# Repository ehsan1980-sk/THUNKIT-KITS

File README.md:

# About #

Thunkit Electronics sells electronic kits for hobbyists and engineers alike. Available at [thunkitelectronics.com](https://thunkitelectronics.com) and [Tindie](https://www.tindie.com/stores/cmccaskey). All designs are open source with schematics, board layouts, code, and BOMs freely available.

## In This Repository ##
| POGO ICSP | BREADBOARD ICSP | LOGIC-KEYCHAIN | MAKIT-THT | T85DUINO |
| ------------------------------------------ | ----------------------------------------- | ----------------------------------------- | ----------------------------------------- | ----------------------------------------- |
|  |  |  |  |  |
| Spring loaded pogo pins for AVR ICSP programming | Breakout for AVR ICSP Cable | D flip-flop SMD soldering keychain kit | DIY 100% Through-hole Arduino kit | DIY 100% Through-hole Mini Arduino kit |

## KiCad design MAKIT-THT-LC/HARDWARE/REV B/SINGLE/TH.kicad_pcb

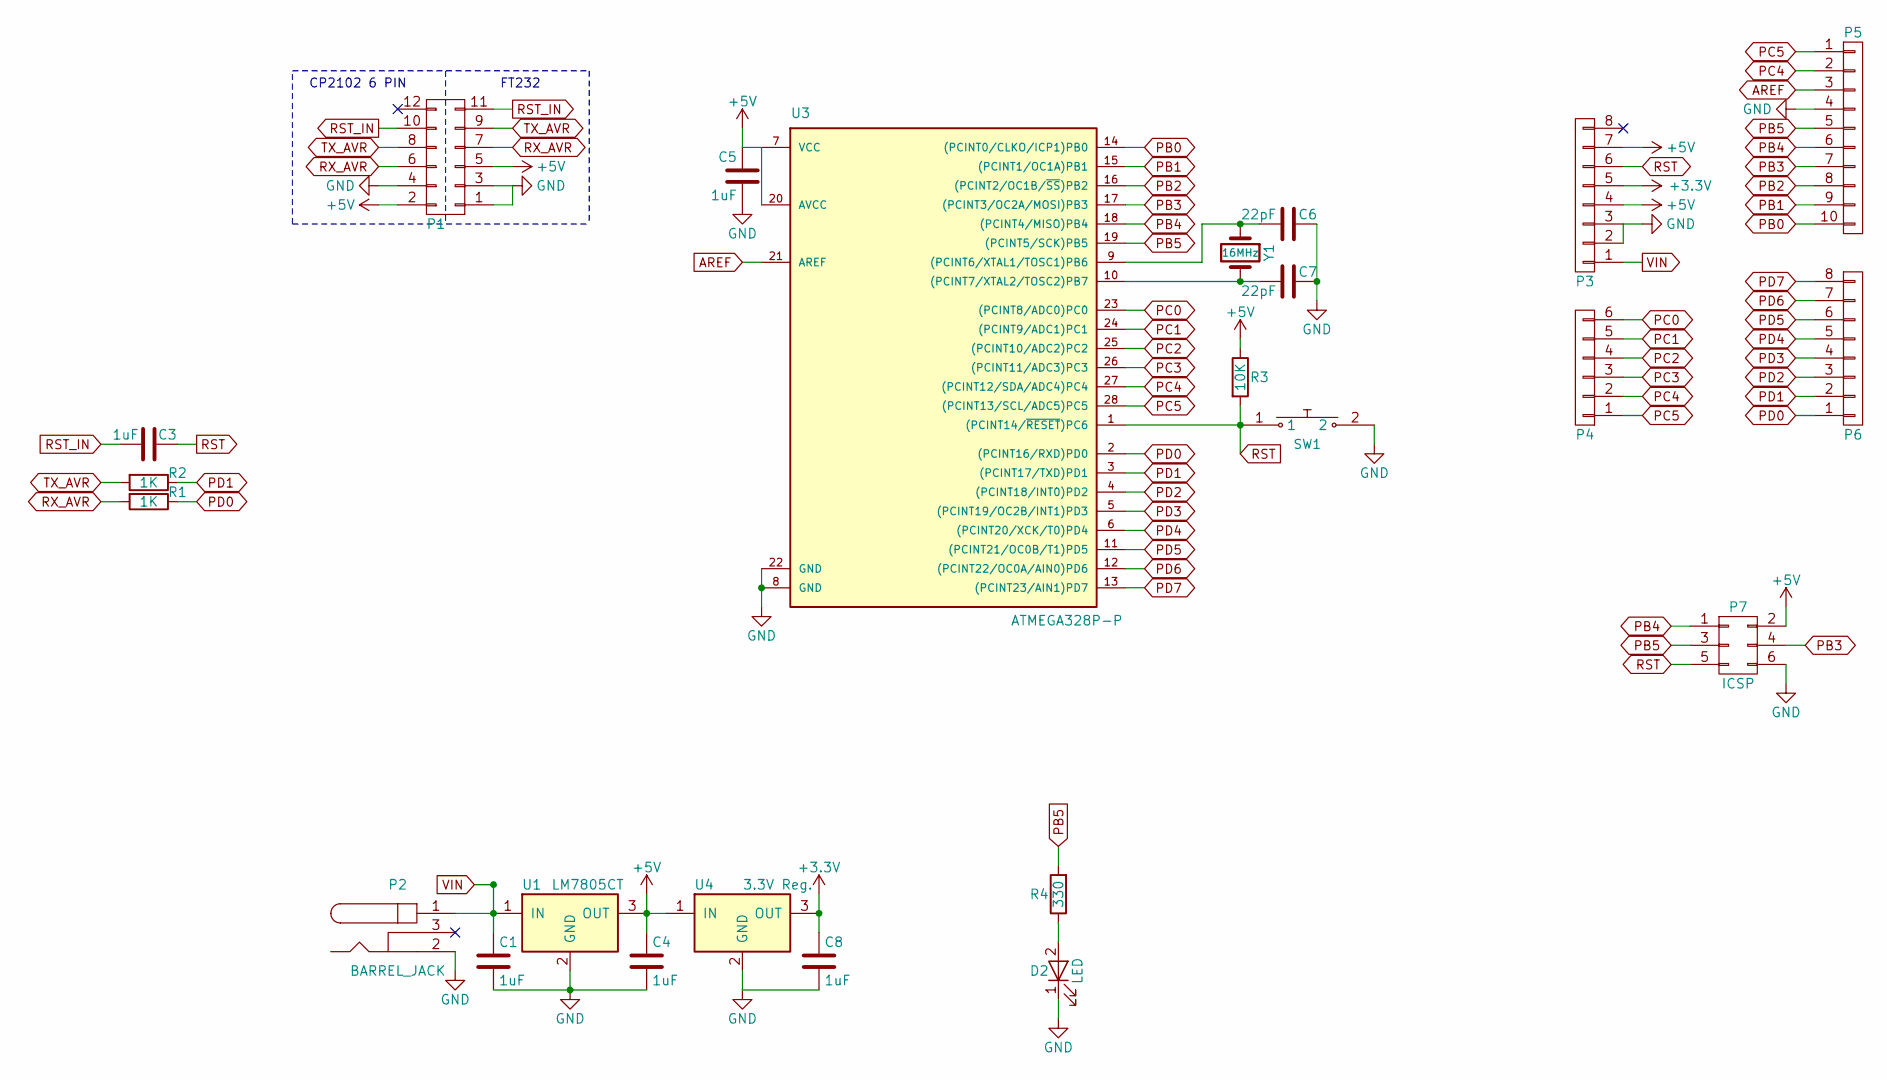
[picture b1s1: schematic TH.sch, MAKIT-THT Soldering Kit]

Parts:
C1, C3, C4, C5, C8: 1uF; C_Disc_D3.8mm_W2.6mm_P2.50mm
C6, C7: 22pF; C_Disc_D3.8mm_W2.6mm_P2.50mm
D2: LED; LED_D5.0mm
P1: CONN_02X06; Pin_Header_Angled_2x06
P2: BARREL_JACK
P3, P6: CONN_01X08; Pin_Header_Straight_1x08_Pitch2.54mm
P4: CONN_01X06; Pin_Header_Straight_1x06_Pitch2.54mm
P5: CONN_01X10; Pin_Header_Straight_1x10_Pitch2.54mm
P7: ICSP; Pin_Header_Straight_2x03_Pitch2.54mm
R1, R2: 1K; R_Axial_DIN0207_L6.3mm_D2.5mm_P7.62mm_Horizontal
R3: 10K; R_Axial_DIN0207_L6.3mm_D2.5mm_P7.62mm_Horizontal
R4: 330; R_Axial_DIN0207_L6.3mm_D2.5mm_P7.62mm_Horizontal
SW1: Push_SW; SW_PUSH_6mm
U1: LM7805CT; TO-220-3_Horizontal_NO_HOLE
U3: ATMEGA328P-P; DIP-28_W7.62mm_LongPads
U4: 3.3V Reg.; TO-92_Inline_Wide
Y1: 16MHz; Crystal_HC49-U_Vertical

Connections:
+3V3: C8.1, P3.5, U4.3 (OUT)
+5V: C4.1, C5.1, P1.2, P1.5, P3.4, P3.7, P7.2, R3.1, U1.3 (OUT), U3.7 (VCC), U3.20 (AVCC), U4.1 (IN)
AREF: P5.3, U3.21 (AREF)
GND: C1.2, C4.2, C5.2, C6.1, C7.1, C8.2, D2.1 (K), P1.1, P1.3, P1.4, P2.2, P3.2, P3.3, P5.4, P7.6, SW1.2, U1.2 (GND), U3.8 (GND), U3.22 (GND), U4.2 (GND)
unnamed: C6.2, U3.9 ((PCINT6/XTAL1/TOSC1)PB6), Y1.1
unnamed: C7.2, U3.10 ((PCINT7/XTAL2/TOSC2)PB7), Y1.2
unnamed: D2.2 (A), R4.1
PB0: P5.10, U3.14 ((PCINT0/CLKO/ICP1)PB0)
PB1: P5.9, U3.15 ((PCINT1/OC1A)PB1)
PB2: P5.8, U3.16 ((PCINT2/OC1B/~SS~)PB2)
PB3: P5.7, P7.4, U3.17 ((PCINT3/OC2A/MOSI)PB3)
PB4: P5.6, P7.1, U3.18 ((PCINT4/MISO)PB4)
PB5: P5.5, P7.3, R4.2, U3.19 ((PCINT5/SCK)PB5)
PC0: P4.6, U3.23 ((PCINT8/ADC0)PC0)
PC1: P4.5, U3.24 ((PCINT9/ADC1)PC1)
PC2: P4.4, U3.25 ((PCINT10/ADC2)PC2)
PC3: P4.3, U3.26 ((PCINT11/ADC3)PC3)
PC4: P4.2, P5.2, U3.27 ((PCINT12/SDA/ADC4)PC4)
PC5: P4.1, P5.1, U3.28 ((PCINT13/SCL/ADC5)PC5)
PD0: P6.1, R1.1, U3.2 ((PCINT16/RXD)PD0)
PD1: P6.2, R2.1, U3.3 ((PCINT17/TXD)PD1)
PD2: P6.3, U3.4 ((PCINT18/INT0)PD2)
PD3: P6.4, U3.5 ((PCINT19/OC2B/INT1)PD3)
PD4: P6.5, U3.6 ((PCINT20/XCK/T0)PD4)
PD5: P6.6, U3.11 ((PCINT21/OC0B/T1)PD5)
PD6: P6.7, U3.12 ((PCINT22/OC0A/AIN0)PD6)
PD7: P6.8, U3.13 ((PCINT23/AIN1)PD7)
RST: C3.2, P3.6, P7.5, R3.2, SW1.1, U3.1 ((PCINT14/~RESET~)PC6)
RST_IN: C3.1, P1.10, P1.11
RX_AVR: P1.6, P1.7, R1.2
TX_AVR: P1.8, P1.9, R2.2
VIN: C1.1, P2.1, P3.1, U1.1 (IN)

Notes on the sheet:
FT232
CP2102 6 PIN

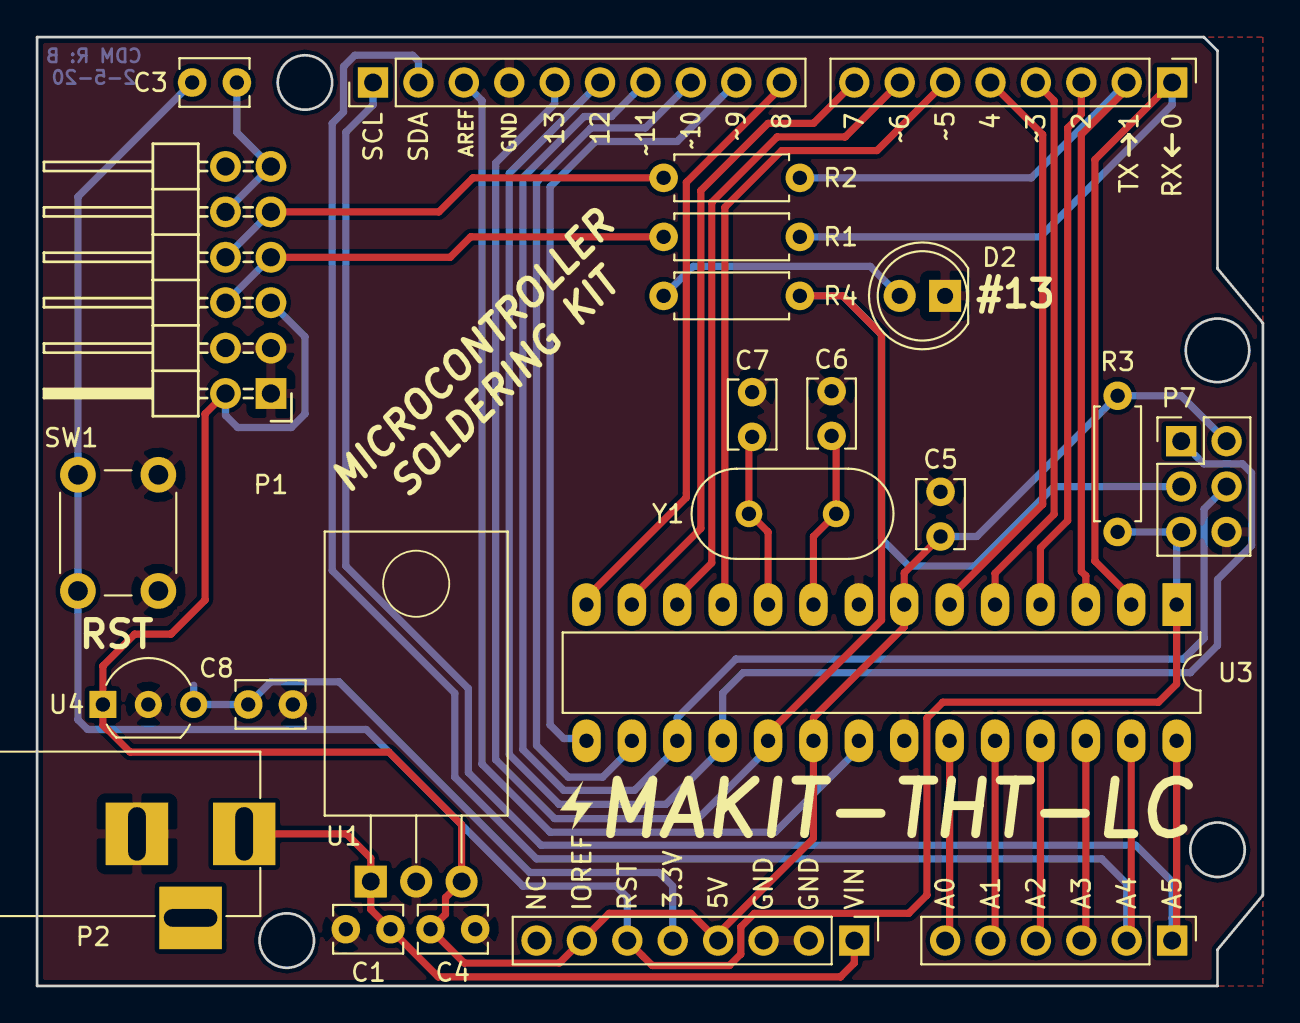
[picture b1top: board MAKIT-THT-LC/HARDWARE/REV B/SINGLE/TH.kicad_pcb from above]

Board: 2 copper layers, 68.6 x 53.1 mm, 24 parts (0 on the bottom side), 32 nets.

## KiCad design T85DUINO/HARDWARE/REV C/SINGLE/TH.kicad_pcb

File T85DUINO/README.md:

# About #

Thunkit Electronics sells electronic kits for hobbyists and engineers alike. Available at [thunkitelectronics.com](https://thunkitelectronics.com) and [Tindie](https://www.tindie.com/stores/cmccaskey). All designs are open source with schematics, board layouts, code, and BOMs freely available.

## Description ###
 <br />
The T85DUINO is a mini Arduino board featuring the ATTiny85. The T85DUINO is a 3V board powered by a CR1025 battery making this a great choice to show off your soldering and programming skills if you choose to wear it as a badge.

## Why T85DUINO? ##
The T85DUINO is a mini Arduino kit. This makes the T85DUINO a simple yet fun soldering kit that has the added value of being a development board for the ATtiny85 after assembly. The T85DUINO can be used as a development board, directly in your project, or even a badge to show off your soldering and programming skills.

## Technical Specifications ##

The T85DUINO uses the ATtiny85 as the main microconroller. The ATtiny85 is flashed with Gemma boot by Adafruit that allows the T85DUINO to be reprogrammed in the Arduino IDE. 

The T85DUINO runs directly off of 3V from a CR1025 battery. While this is enough to blink the on-board LED, it is posible to brown out the microcontroller if the external connections on the board are used without consideration to this fact.

Since the T85DUINO runs at 3V, the board only requires the 68 Ohm termination resistors for USB and doesn't require the zener diodes to limit the USB data line voltages.

The T85DUINO has an on-board LED that can be blinked to emulate the famous Blink Arduino Sketch.

## Schematic ##
PDF coming soon...Please check KiCad files

## Bill of Material ##
PDF coming soon...Please check KiCad files

## Soldering Instructions ##
Coming soon...

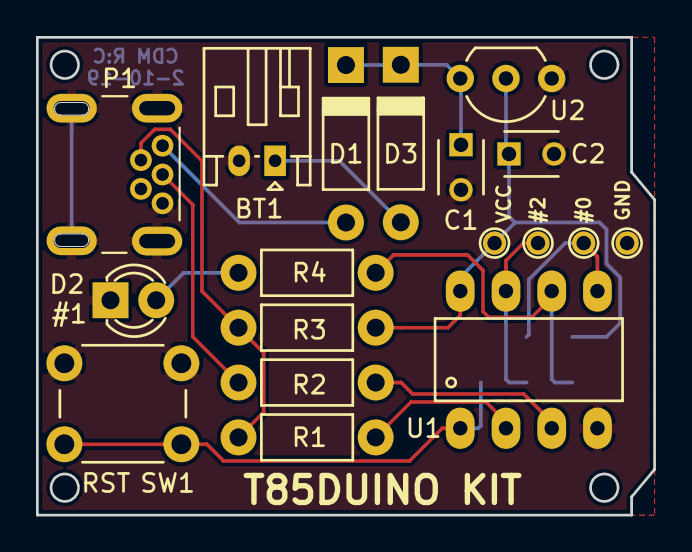
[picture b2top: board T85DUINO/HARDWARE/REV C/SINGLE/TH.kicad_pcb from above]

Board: 2 copper layers, 34.3 x 26.5 mm, 19 parts (1 on the bottom side), 14 nets.

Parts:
BT1: JST-PH; JST_PH_S2B-PH-K_02x2.00mm_Angled
C1, C2: 1uF; C_Disc_D3_P2.5
D1, D3: D_Schottky; DO-41_Short
D2: LED; LED-3MM
P1: USB_OTG; USB_MINI_B_TH
P2: ICSP; 2.54 ICSP
R1, R2: 68; Resistor_Horizontal_RM7mm
R3: 1.5K; Resistor_Horizontal_RM7mm
R4: 330; Resistor_Horizontal_RM7mm
SW1: Push_SW; SW_PUSH_6mm
TP1, TP2, TP3, TP4: TEST; PINTST
U1: ATTINY85-P; DIP-8
U2: AP1117; TO-92_Inline_Wide

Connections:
GND: BT1.2, C1.2, C2.2, D2.1, P1.5, P1.6, P2.6, SW1.2, TP3.1, U1.4, U2.1
MISO: P2.1, R4.2, U1.6
MOSI: P2.4, TP1.1, U1.5
unnamed: BT1.1, D3.2
unnamed: C1.1, D1.1, D3.1, U2.3
unnamed: D2.2, R4.1
unnamed: P1.2, R1.2, R3.2
unnamed: P1.3, R2.2
unnamed: R1.1, U1.2
unnamed: R2.1, U1.3
RST: P2.5, SW1.1, U1.1
SCK: P2.3, TP2.1, U1.7
VBUS: D1.2, P1.1
VCC: C2.1, P2.2, R3.1, TP4.1, U1.8, U2.2

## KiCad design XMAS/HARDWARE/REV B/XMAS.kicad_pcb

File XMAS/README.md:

# About #

Thunkit Electronics sells electronic kits for hobbyists and engineers alike. Available at [thunkitelectronics.com](https://thunkitelectronics.com) and [Tindie](https://www.tindie.com/stores/cmccaskey). All designs are open source with schematics, board layouts, code, and BOMs freely available.

## Description ###
 <br />
The Thunkit Electronics Christmas Ornament is a trendy PCB christmas ornament that lights up 18 cool while LEDs in a spiral pattern. This is light sensitive and only triggers in the dark in 30 second intervals. Powered by a CR2032 battery, battery life is approximately 4 months due to the heavy use of interrupts for timing.

Note: Board shown is REV A, REV B has small tweaks to the layout and the removal of the bodge wire near the microcontroller.

## Schematic ##

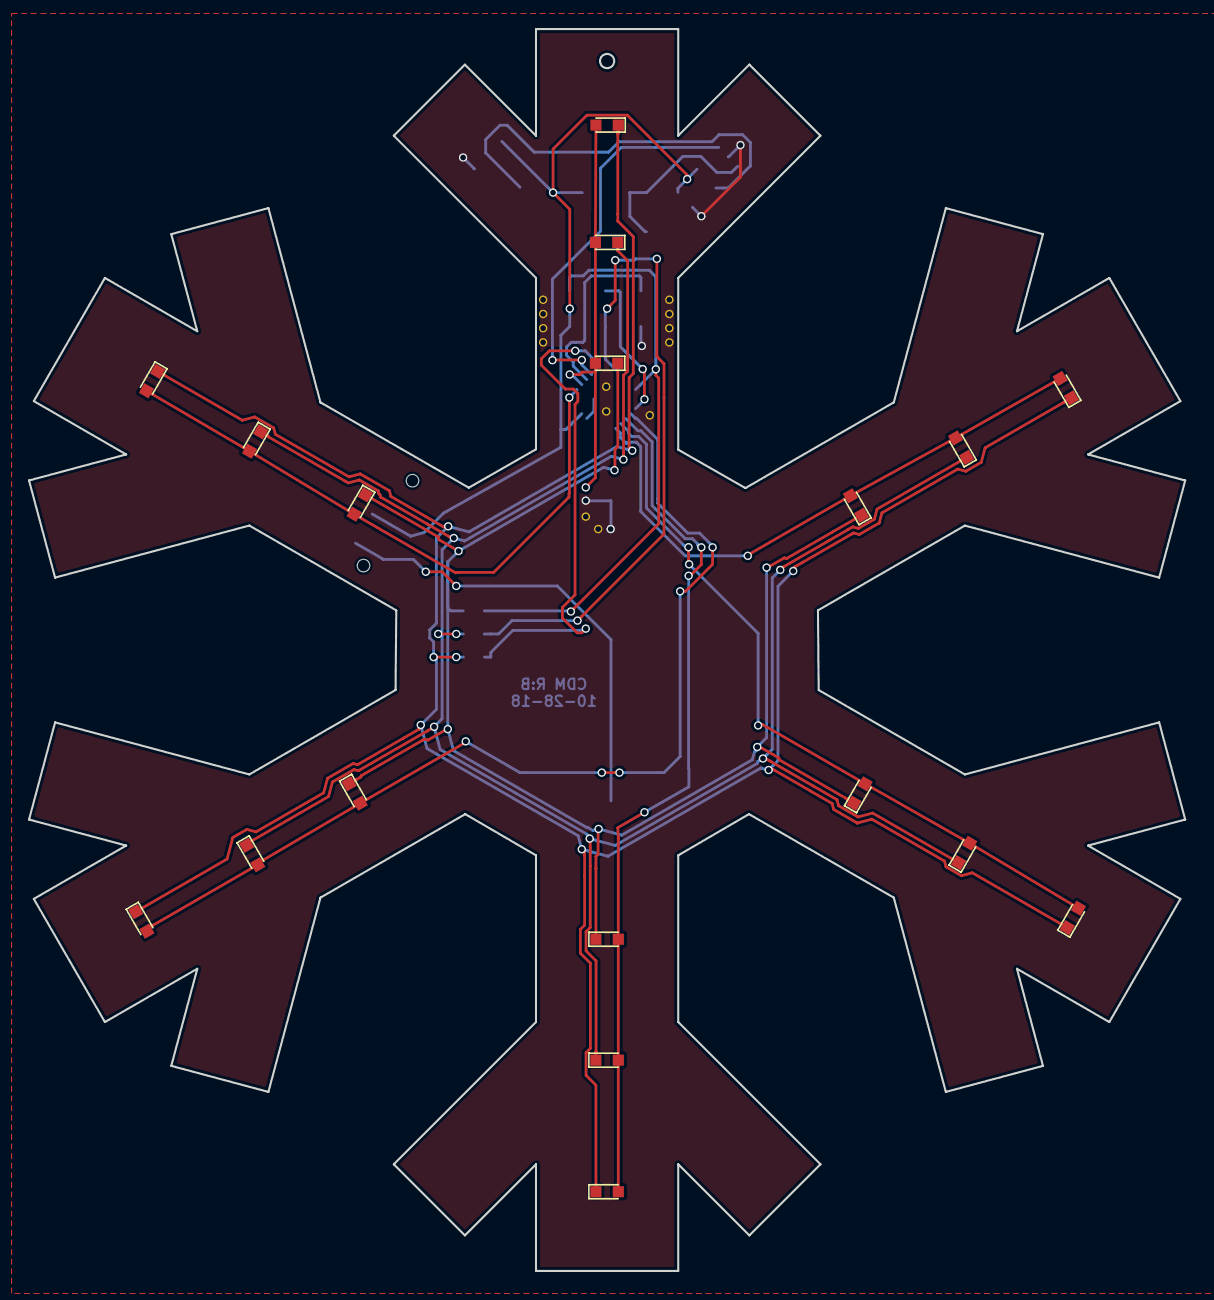
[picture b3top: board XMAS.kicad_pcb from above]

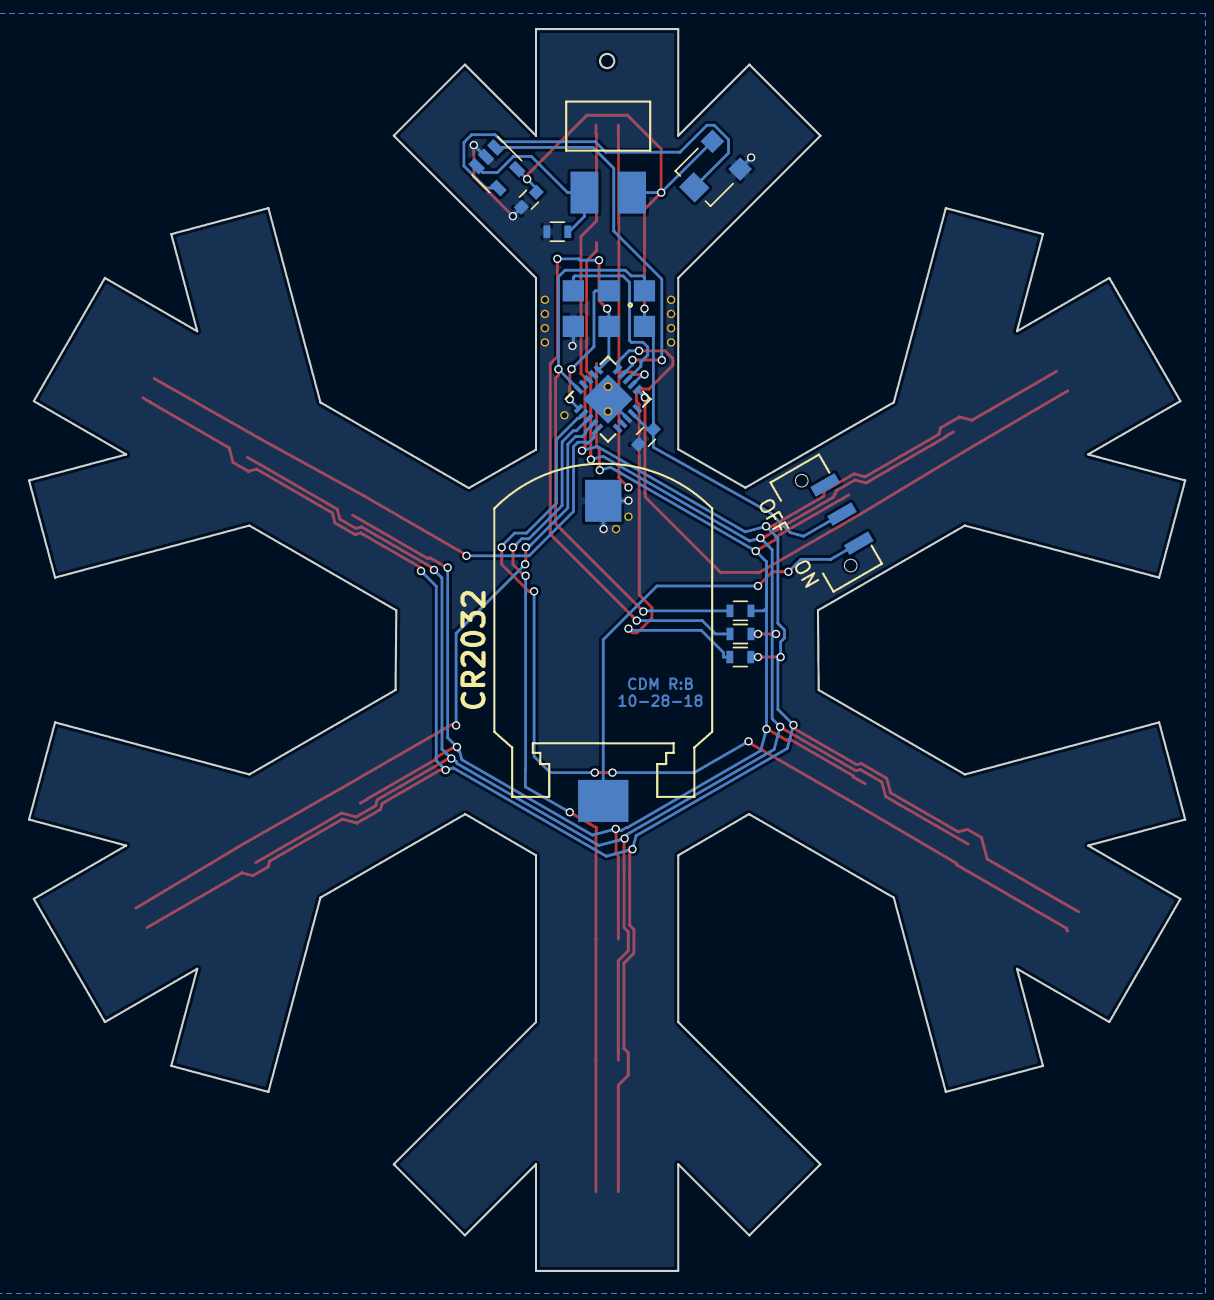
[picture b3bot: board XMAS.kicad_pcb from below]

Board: 2 copper layers, 82.6 x 88.7 mm, 31 parts (13 on the bottom side), 20 nets.

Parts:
BT1: CR2032; CR2032HARWIN
C1, C2: C; C_0603
D1, D2, D3, D4, D5, D6, D7, D8, D9, D10, D11, D12, D13, D14, D15, D16, D17, D18: LED; LED_0603
P1: ICSP; 2.54 ICSP
R1, R2, R3, R8: R; R_0603
R7: R_PHOTO; SMT_PHOTORESISTOR
RV1: POT; Potentiometer_Trimmer-EVM3E
SW1: Push_SW; JS102011JAQN_Handsoldering
U1: MCP6541T-I/LT; SOT-23-5
U2: ATTINY24A-M; QFN-20-1EP_4x4mm_Pitch0.5mm

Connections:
A1: D1.2, D7.2, D13.2, U2.5
A2: D2.2, D8.2, D14.2, U2.4
A3: D3.2, D9.2, D15.2, U2.3
A4: D4.2, D10.2, D16.2, U2.2
A5: D5.2, D11.2, D17.2, U2.11
A6: D6.2, D12.2, D18.2, U2.12
C1: P1.1, R1.1, U2.20
C2: P1.4, R2.1, U2.16
C3: R3.1, U2.15
GND: BT1.2, C1.2, C2.1, P1.6, R8.2, RV1.1, U1.2, U2.8
INT0_AVR: U1.1, U2.14
unnamed: BT1.1, SW1.1
unnamed: D1.1, D2.1, D3.1, D4.1, D5.1, D6.1, R1.2
unnamed: D7.1, D8.1, D9.1, D10.1, D11.1, D12.1, R2.2
unnamed: D13.1, D14.1, D15.1, D16.1, D17.1, D18.1, R3.2
unnamed: R7.2, R8.1, U1.3
unnamed: RV1.2, U1.4
RST: P1.5, U2.13
SCK: P1.3, U2.1
VCC: C1.1, C2.2, P1.2, R7.1, RV1.3, SW1.2, U1.5, U2.9

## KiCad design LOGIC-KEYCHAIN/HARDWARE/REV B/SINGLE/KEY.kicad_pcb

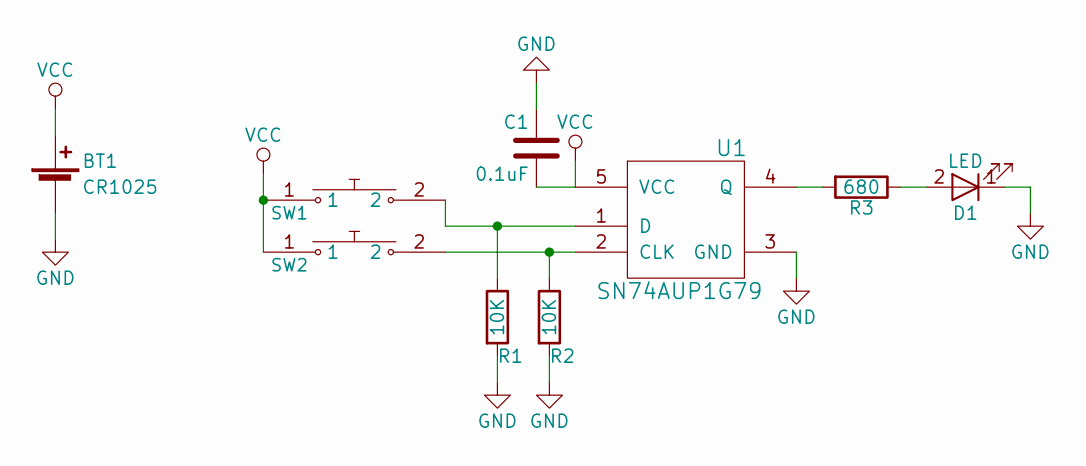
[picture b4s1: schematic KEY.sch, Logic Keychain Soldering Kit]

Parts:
BT1: CR1025; BK-870
C1: 0.1uF; C_0603
D1: LED; LED_0603
R1, R2: 10K; R_0603
R3: 680; R_0603
SW1, SW2: Push_SW; PTS810 SJK 250 SMTR LFS_Handsoldering
U1: SN74AUP1G79; SOT-23-5

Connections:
GND: BT1.2 (-), C1.1, D1.1 (K), R1.2, R2.2, U1.3 (GND)
unnamed: D1.2 (A), R3.1
unnamed: R1.1, SW1.2, U1.1 (D)
unnamed: R2.1, SW2.2, U1.2 (CLK)
unnamed: R3.2, U1.4 (Q)
VCC: BT1.1 (+), C1.2, SW1.1, SW2.1, U1.5 (VCC)

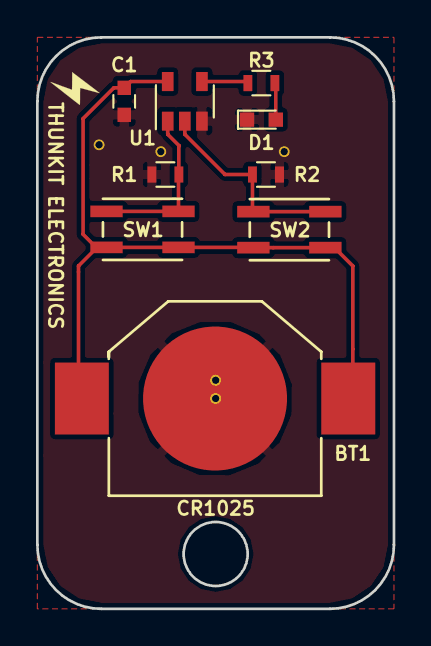
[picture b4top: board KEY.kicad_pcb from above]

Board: 2 copper layers, 19.8 x 31.8 mm, 9 parts (0 on the bottom side), 6 nets.

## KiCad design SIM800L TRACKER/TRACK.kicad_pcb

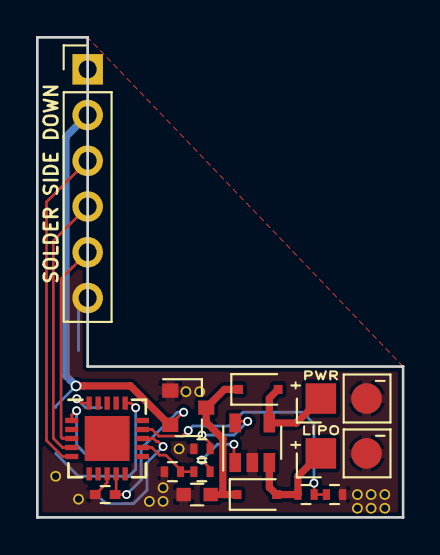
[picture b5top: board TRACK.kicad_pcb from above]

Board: 2 copper layers, 20.3 x 26.7 mm, 16 parts (1 on the bottom side), 16 nets.

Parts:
BT1: 1S; Pin_Header_Straight_1x02_Pitch2.54mm
C1: 4.7uF; C_0603
C2: 1uF; C_0402
D1, D2: S; D_SOD-323F
P1: PWR; Pin_Header_Straight_1x02_Pitch2.54mm
P2: ICSP; 2.54 ICSP
P3: SIM800L Coreboard; Pin_Header_Straight_1x06_Pitch2.54mm
R1, R2, R4, R5: 10K; R_0402
R3: 2K; R_0402
U1: MCP73831T; SOT-23-5
U2: AP1117; SOT-23
U3: ATTINY841-MU; QFN-20-1EP_4x4mm_Pitch0.5mm

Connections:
AVR_RST: P2.5, U3.13
BT_VCC: R4.1, R5.2, U3.14
CHRG_STAT: R1.2, R2.1, U3.12
GND: BT1.2, C1.2, C2.2, P1.2, P2.6, P3.6, R1.1, R3.2, R5.1, U1.2, U2.1, U3.8
MISO: P2.1, U3.20
MOSI: P2.4, U3.16
unnamed: BT1.1, D2.2, R4.2, U1.3
unnamed: D1.2, P1.1, U1.4
unnamed: R2.2, U1.1
unnamed: R3.1, U1.5
SCK: P2.3, U3.1
SIM_RST: P3.3, U3.5
SIM_RX: P3.4, U3.4
SIM_TX: P3.5, U3.3
VCC: C2.1, P2.2, P3.2, U2.2, U3.9
VIN: C1.1, D1.1, D2.1, U2.3

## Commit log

2018-07-04 test3
2018-07-04 fixed gitignore file
2018-07-04 test4
2018-07-16 replaced A7 for SIM 800L
2018-09-09 file recovery and updates
2018-09-22 fixed breadboard layer issues
2018-09-24 logic keychain D FF update
2018-10-09 MAKIT-THT REV C
2018-10-10 keychain FF BOM matches schematic
2018-10-15 readme and images
2018-10-15 readme updates
2018-10-15 MAKIT rev c
2018-10-24 readme update
2018-10-24 readme link fix
2018-10-24 link fix
2018-11-07 added some repos, changed names of others
2018-11-07 added christmas ornament
2018-11-08 removed makit soldering inst, updated readme
2018-11-08 fixed readme image links
2018-11-08 fixed T85DUINO readme
2018-11-08 readme
2018-11-11 updated title block
2018-11-11 rev b and license
2018-11-25 updated XMAS
2018-12-08 readme, code, makefile
2019-03-18 march update
2019-04-23 updated vreg
2019-04-23 3.3V Reg BOM update
2020-03-17 added MAKIT-THT-LC
2020-03-17 cleanup
2022-01-31 Create Think it-Arduino Uno
